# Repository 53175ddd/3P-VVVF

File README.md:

# 3P-VVVF

自作三相インバータのオープンソースプロジェクト

# 目標

200V の三相モータを駆動できるインバータキットの製作

現在開発中

# フォルダ構成

- `Arduino/` // Arduino プロジェクトの開発場所
  - [`VVVF/VVVF.ino`](./Arduino/VVVF/VVVF.ino) // スタンダードな VVVF のプログラム
- `Bridge/` // 基板の開発場所

# LICENCE

<p xmlns:cc="http://creativecommons.org/ns#" xmlns:dct="http://purl.org/dc/terms/"><a property="dct:title" rel="cc:attributionURL" href="https://github.com/53175ddd/3P-VVVF">3P-VVVF</a> by <a rel="cc:attributionURL dct:creator" property="cc:attributionName" href="https://twitter.com/53175ddd">MOS@53175ddd</a> is licensed under <a href="https://creativecommons.org/licenses/by-nc-sa/4.0/deed.ja" target="_blank" rel="license noopener noreferrer" style="display:inline-block;">CC BY-NC-SA 4.0</a></p>

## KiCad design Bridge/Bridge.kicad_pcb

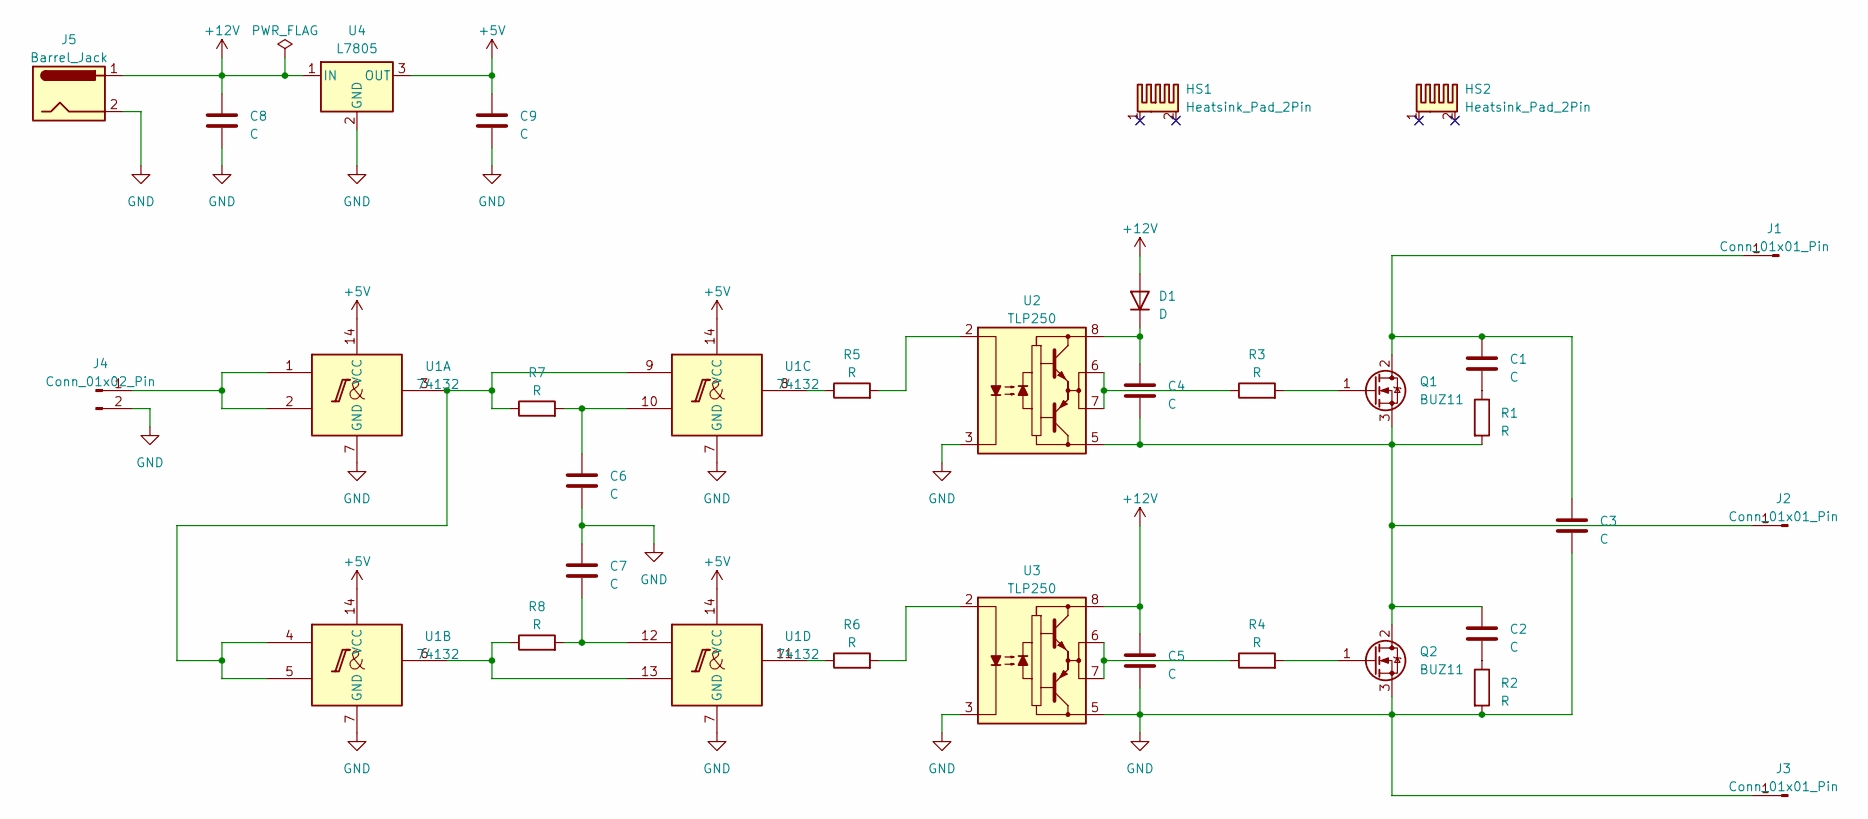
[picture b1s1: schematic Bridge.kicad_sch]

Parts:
C1, C2, C4, C5, C6, C7, C8, C9: C; C_Disc_D6.0mm_W2.5mm_P5.00mm
C3: C; C_Axial_L17.0mm_D7.0mm_P20.00mm_Horizontal
D1: D; D_A-405_P7.62mm_Horizontal
HS1, HS2: Heatsink_Pad_2Pin; 16PB017
J1, J2, J3: Conn_01x01_Pin; Screw-on-Board
J4: Conn_01x02_Pin; PinSocket_1x02_P2.54mm_Vertical
J5: Barrel_Jack; BarrelJack_Horizontal
Q1, Q2: BUZ11; TO-247-3_Vertical
R1, R2, R3, R4, R5, R6, R7, R8: R; R_Axial_DIN0204_L3.6mm_D1.6mm_P7.62mm_Horizontal
U1: 74132; DIP-14_W7.62mm
U2, U3: TLP250; DIP-8_W7.62mm
U4: L7805; TO-220-3_Vertical

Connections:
+5V: C9.1, U1.14 (VCC), U4.3 (OUT)
+12V: C5.1, C8.1, D1.2 (A), J5.1, U3.8 (VCC), U4.1 (IN)
GND: C3.2, C5.2, C6.2, C7.1, C8.2, C9.2, J3.1, J4.2, J5.2, Q2.3 (S), R2.2, U1.7 (GND), U2.3 (C), U3.3 (C), U3.5 (VEE), U4.2 (GND)
unnamed: C1.2, R1.1
unnamed: C2.2, R2.1
unnamed: C6.1, R7.2, U1.10
unnamed: C7.2, R8.2, U1.12
unnamed: C4.1, D1.1 (K), U2.8 (VCC)
unnamed: C1.1, C3.1, J1.1, Q1.2 (D)
unnamed: C2.1, C4.2, J2.1, Q1.3 (S), Q2.2 (D), R1.2, U2.5 (VEE)
unnamed: J4.1, U1.1, U1.2
unnamed: Q1.1 (G), R3.2
unnamed: Q2.1 (G), R4.2
unnamed: R3.1, U2.6 (VO), U2.7 (VO)
unnamed: R4.1, U3.6 (VO), U3.7 (VO)
unnamed: R5.1, U1.8
unnamed: R6.1, U1.11
unnamed: R7.1, U1.3, U1.4, U1.5, U1.9
unnamed: R8.1, U1.6, U1.13
unnamed: R5.2, U2.2 (A)
unnamed: R6.2, U3.2 (A)

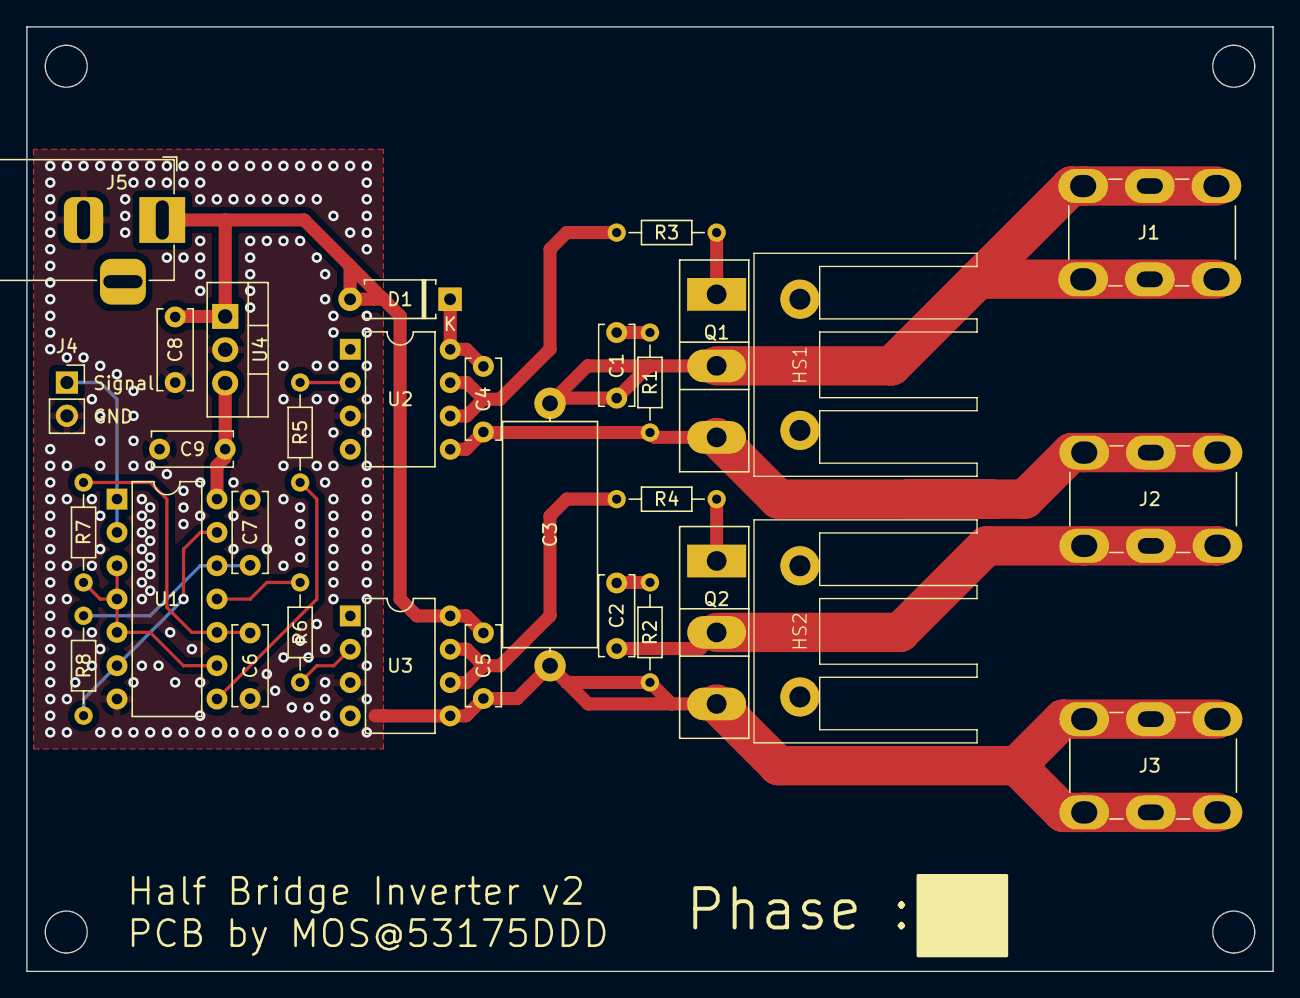
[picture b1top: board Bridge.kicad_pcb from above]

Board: 2 copper layers, 95.0 x 72.0 mm, 31 parts (0 on the bottom side), 21 nets.

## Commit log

2023-10-17 first commit (write readme, create circuit, and pcb design)
2023-10-17 edit readme
2023-10-18 edit silkscreen
2023-10-26 change link
2023-11-19 PCB を v2 に update
